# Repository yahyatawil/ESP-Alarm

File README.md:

# ESP-Alarm
This project was built for [Allaboutcircuit](https://www.allaboutcircuits.com/projects/esp-alarm-set-alarms-from-your-mobile-phone-esp8266-arduino-uno-wifi-iot/) published in 2017. 

## Hardware 
* Arduino UNO or any compatible board (optional).
* ATmega328P (optional).
* ESP8266 Wi-Fi module, ESP-01 model.
* 1.44-inch TFT display module.
* TP4056 breakout board (Li-ion battery charger).
* DS1307 (RTC chip)
* 74LVX4245 (5V-3V3 level converter)
* USB TTL converter cable (optional)

## Software / Arduino code
The code depends on the following libraries:

* TFT_ILI9163
* Adafruit_GFX
* DS1307RTC
* Wire (for I2C connection)
* EEPROM (to store alarms in the internal EEPROM)
* SoftwareSerial (optional debugging)

## Android App 

Many thanks to my friend Jihad Al-bathish (AKA Joud) for developing a native Android application for this project.

## Demo
https://www.youtube.com/watch?v=W3wOcIKqi2k

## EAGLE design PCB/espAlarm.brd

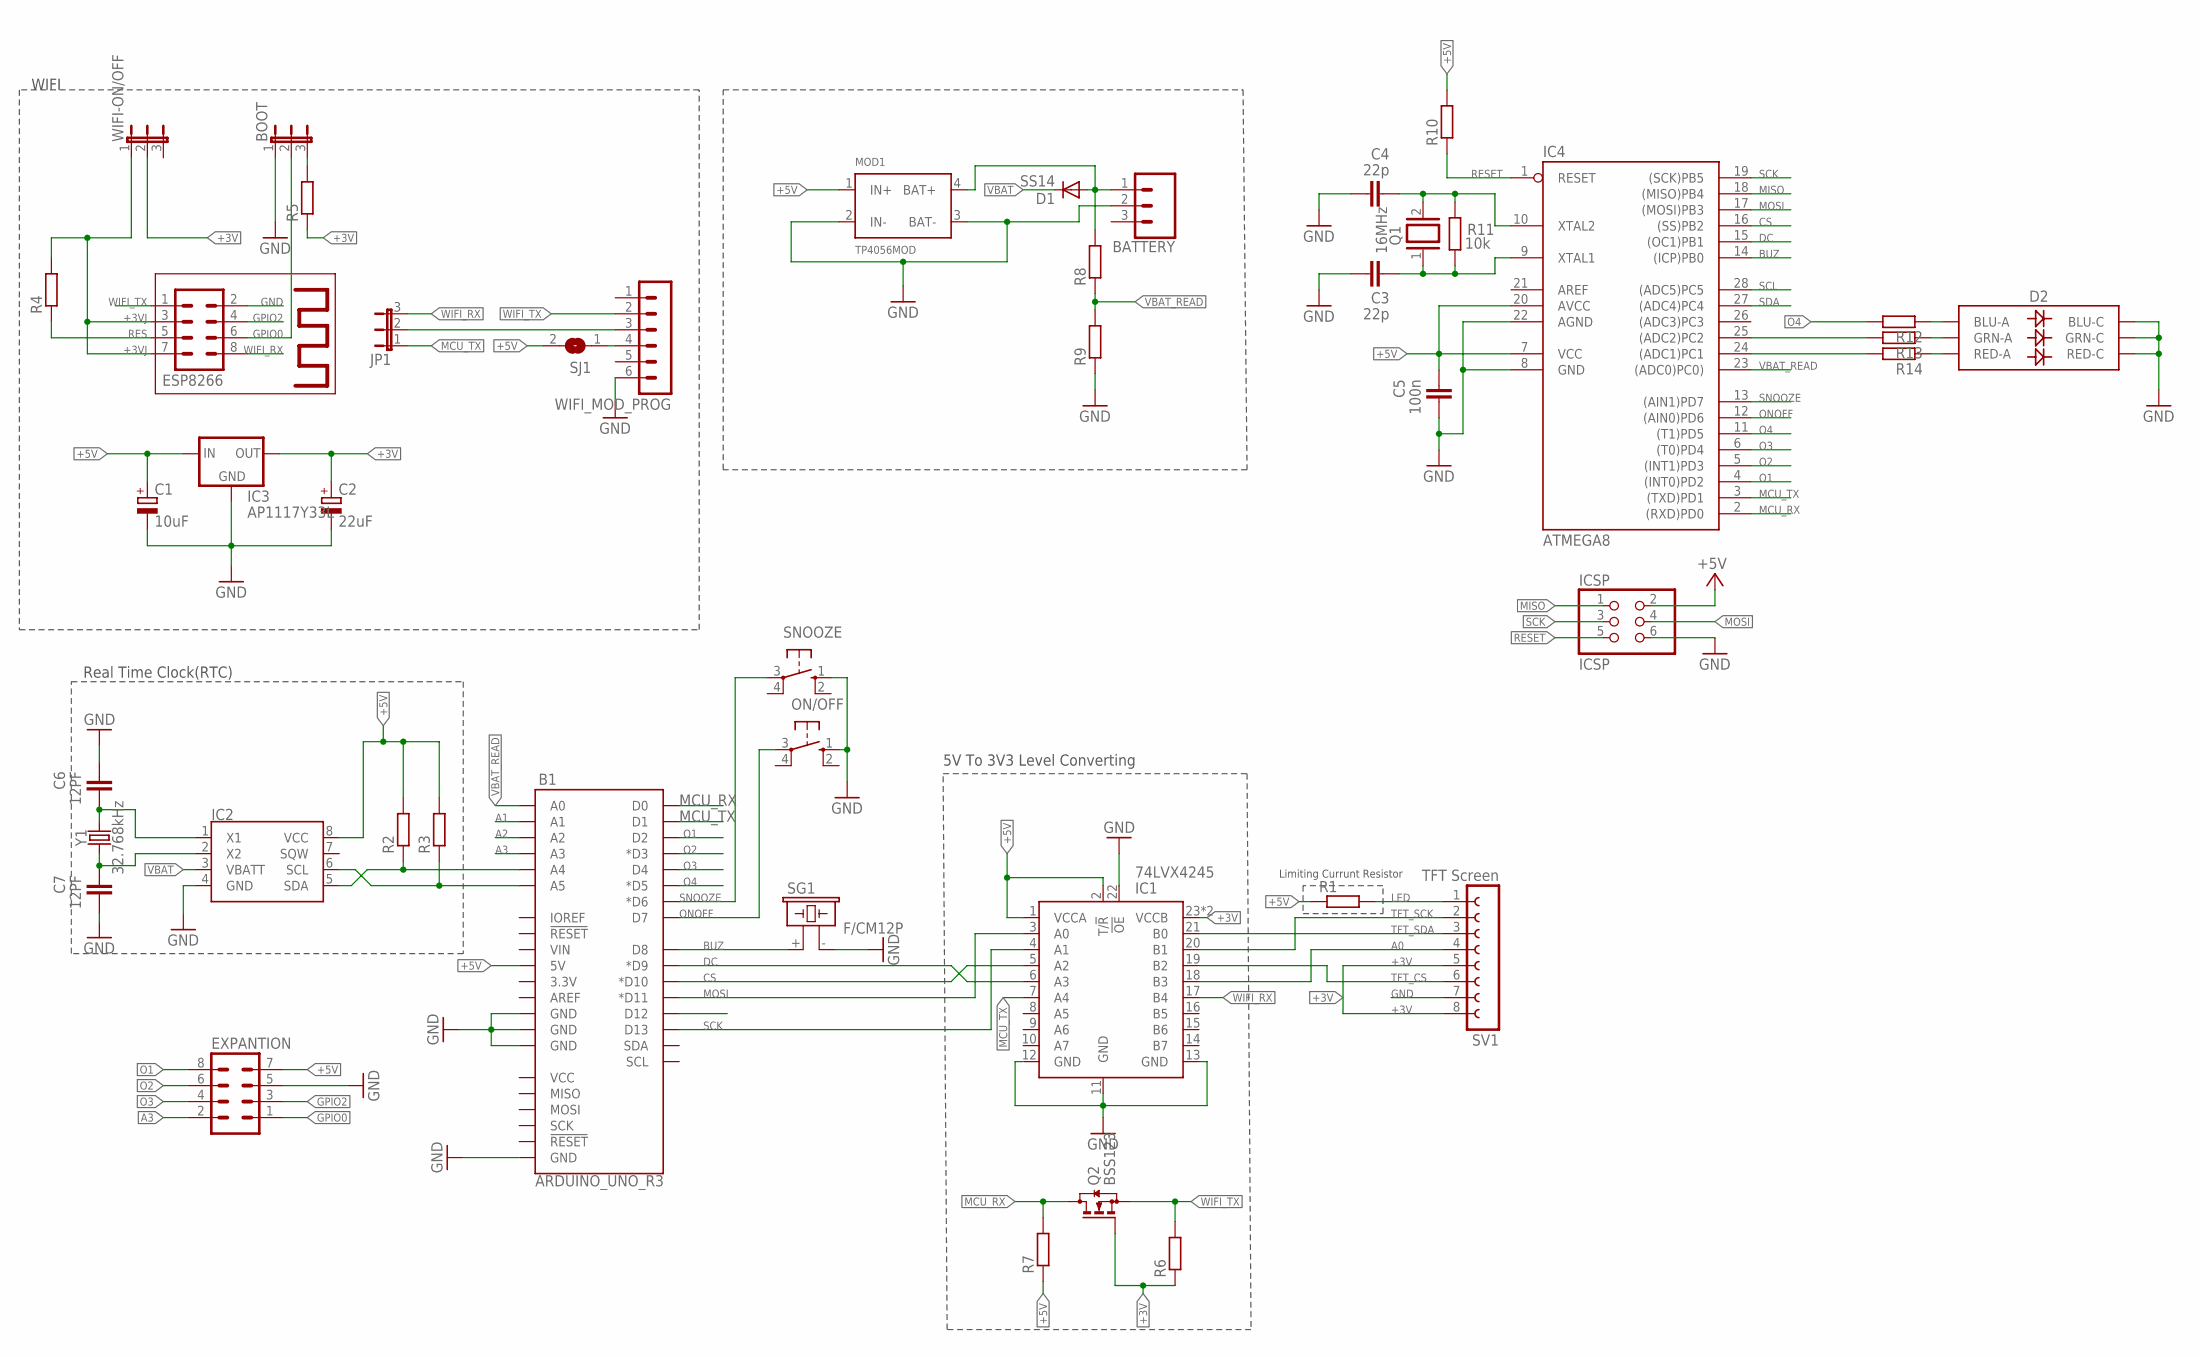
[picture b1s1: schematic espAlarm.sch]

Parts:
B1: ARDUINO_UNO_R3; ARDUINO_R3
BATTERY: CONN_03JST-PTH-VERT; JST-3-PTH-VERT
BOOT: JP2E; JP2
C1: 10uF; E2,5-7
C2: 22uF; E2,5-7
C3, C4: 22p; C0805
C5: 100n; C0805
C6, C7: 12PF; C0805
D1: SS14; DO214AC
D2: LED-RGBNO_IC; LED-TRICOLOR-5050
ESP8266: MA04-2
EXPANTION: MA04-2
IC1: 74LVX4245; TSSOP-24
IC2: DS1307; DIP-08
IC3: AP1117Y33L; SOT-89-3
IC4: ATMEGA8; DIL28-3
ICSP: ICSP; 2X03
JP1: JP2E; JP2
MOD1: TP4056MOD; TP4056BRD
ON/OFF: 10-XX; B3F-10XX
Q1: 16MHz; SMARTPRJ_QS
Q2: BSS123; SOT23
R1, R2, R3, R4, R5, R6, R7, R8, R9, R10, R12, R13, R14: R-EU_M1206; M1206
R11: 10k; M1206
SG1: F/CM12P
SJ1: SJ
SNOOZE: 10-XX; B3F-10XX
SV1: TFT Screen; FE08
WIFI-ON/OFF: JP2E; JP2
WIFI_MOD_PROG: MA06-1
Y1: 32.768kHz; CRYSTAL-PTH-2X6-CYL

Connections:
+3V: C2.+, IC1.23 (VCCB), IC1.24 (VCCB), IC3.3 (OUT), IC3.4 (OUT), Q2.1 (G), R5.1, R6.1, SV1.5, SV1.8, WIFI-ON/OFF.2
+3VJ: ESP8266.3, ESP8266.7, R4.2, WIFI-ON/OFF.1
+5V: B1.5V, C1.+, C5.2, EXPANTION.7, IC1.1 (VCCA), IC1.2 (T/!R), IC2.8 (VCC), IC3.1 (IN), IC4.7 (VCC), IC4.20 (AVCC), ICSP.2, MOD1.1 (IN+), R1.1, R2.2, R3.2, R7.1, R10.2, SJ1.2
A0: IC1.18 (B3), SV1.4
A1: B1.A1, IC4.24 ((ADC1)PC1), R14.2
A2: B1.A2, IC4.25 ((ADC2)PC2), R13.2
A3: B1.A3, EXPANTION.2
AREF: IC4.21 (AREF)
BUZ: B1.D8, IC4.14 ((ICP)PB0), SG1.+ (1)
CS: B1.D10 (*D10), IC1.5 (A2), IC4.16 ((SS)PB2)
DC: B1.D9 (*D9), IC1.6 (A3), IC4.15 ((OC1)PB1)
GND: B1.GND@1 (GND), B1.GND@2 (GND), B1.GND@3 (GND), B1.GND@4 (GND), BATTERY.2, BOOT.1, C1.-, C2.-, C3.1, C4.1, C5.1, C6.2, C7.1, D2.4 (BLU-C), D2.5 (RED-C), D2.6 (GRN-C), ESP8266.2, EXPANTION.5, IC1.11 (GND), IC1.12 (GND), IC1.13 (GND), IC1.22 (!OE), IC2.4 (GND), IC3.2 (GND), IC4.8 (GND), IC4.22 (AGND), ICSP.6, MOD1.2 (IN-), MOD1.3 (BAT-), ON/OFF.1 (S), R9.1, SG1.- (2), SNOOZE.1 (S), SV1.7, WIFI_MOD_PROG.6
GPIO0: BOOT.2, ESP8266.6, EXPANTION.1
GPIO2: ESP8266.4, EXPANTION.3
LED: R1.2, SV1.1
MCU_RX: B1.D0, IC4.2 ((RXD)PD0), Q2.3 (D), R7.2
MCU_TX: B1.D1, IC1.7 (A4), IC4.3 ((TXD)PD1), JP1.1
MISO: IC4.18 ((MISO)PB4), ICSP.1
MOSI: B1.D11 (*D11), IC1.3 (A0), IC4.17 ((MOSI)PB3), ICSP.4
unnamed: JP1.2, WIFI_MOD_PROG.3
unnamed: BOOT.3, R5.2
unnamed: C6.1, IC2.1 (X1), Y1.2
unnamed: C7.2, IC2.2 (X2), Y1.1
unnamed: SJ1.1, WIFI_MOD_PROG.4
unnamed: BATTERY.1, D1.A, MOD1.4 (BAT+), R8.2
unnamed: C3.2, IC4.9 (XTAL1), Q1.1, R11.1
unnamed: C4.2, IC4.10 (XTAL2), Q1.2, R11.2
unnamed: D2.3 (BLU-A), R12.1
unnamed: D2.1 (GRN-A), R13.1
unnamed: D2.2 (RED-A), R14.1
O1: B1.D2, EXPANTION.8, IC4.4 ((INT0)PD2)
O2: B1.D3 (*D3), EXPANTION.6, IC4.5 ((INT1)PD3)
O3: B1.D4, EXPANTION.4, IC4.6 ((T0)PD4)
O4: B1.D5 (*D5), IC4.11 ((T1)PD5), R12.2
ONOFF: B1.D7, IC4.12 ((AIN0)PD6), ON/OFF.3
RES: ESP8266.5, R4.1
RESET: IC4.1 (RESET), ICSP.5, R10.1
SCK: B1.D13, IC1.4 (A1), IC4.19 ((SCK)PB5), ICSP.3
SCL: B1.A5, IC2.6 (SCL), IC4.28 ((ADC5)PC5), R3.1
SDA: B1.A4, IC2.5 (SDA), IC4.27 ((ADC4)PC4), R2.1
SNOOZE: B1.D6 (*D6), IC4.13 ((AIN1)PD7), SNOOZE.3
TFT_CS: IC1.19 (B2), SV1.6
TFT_SCK: IC1.20 (B1), SV1.2
TFT_SDA: IC1.21 (B0), SV1.3
VBAT: D1.C, IC2.3 (VBATT)
VBAT_READ: B1.A0, IC4.23 ((ADC0)PC0)), R8.1, R9.2
WIFI_RX: ESP8266.8, IC1.17 (B4), JP1.3
WIFI_TX: ESP8266.1, Q2.2 (S), R6.2, WIFI_MOD_PROG.2

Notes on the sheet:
5V To 3V3 Level Converting
Limiting Currunt Resistor
Real Time Clock(RTC)
WIFI

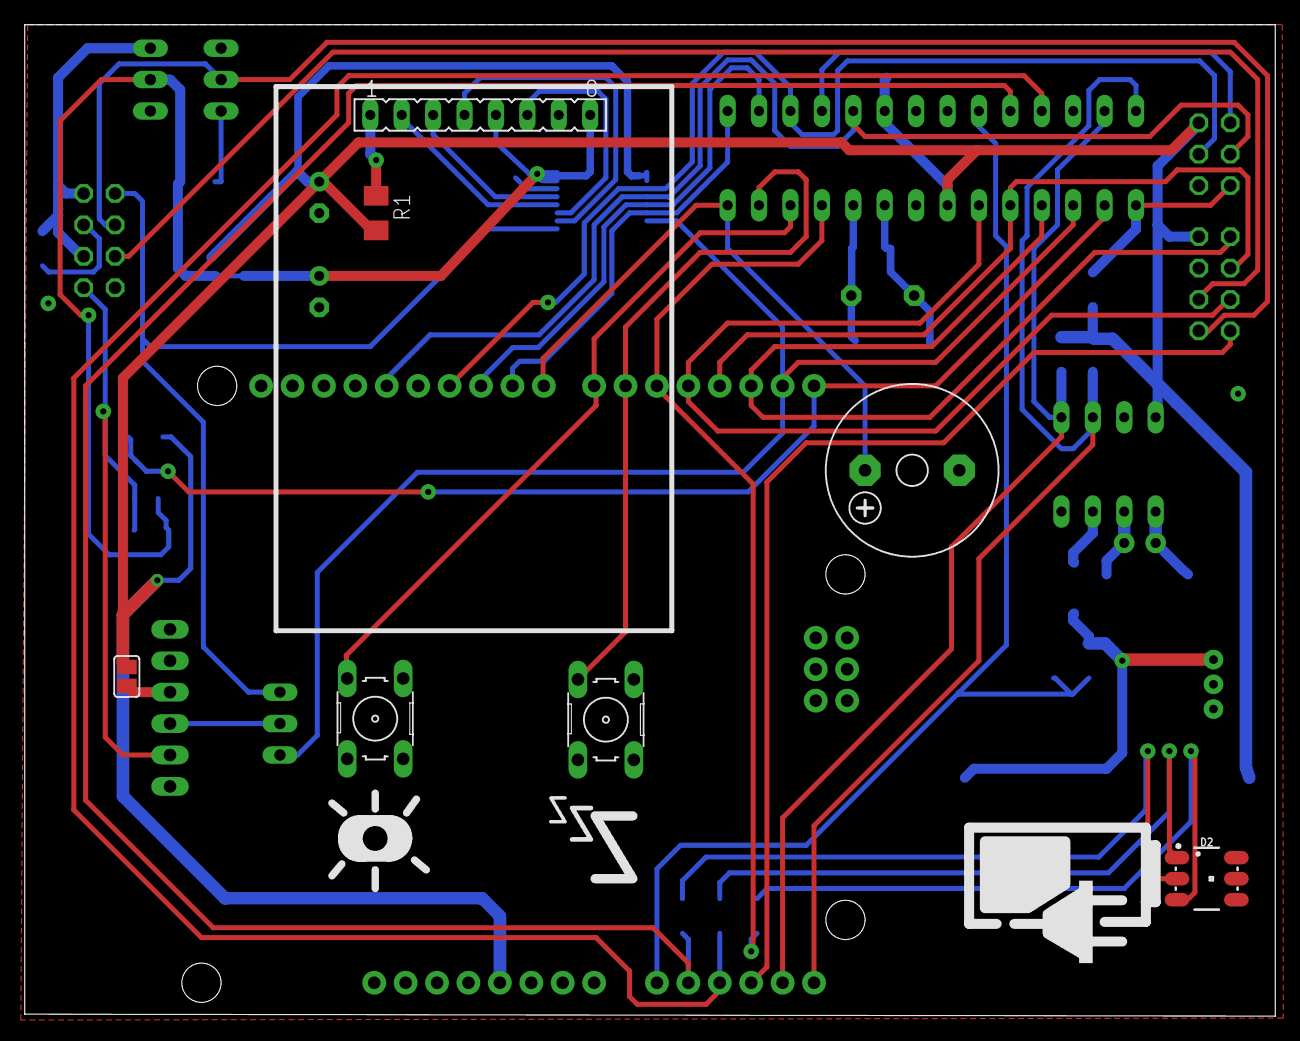
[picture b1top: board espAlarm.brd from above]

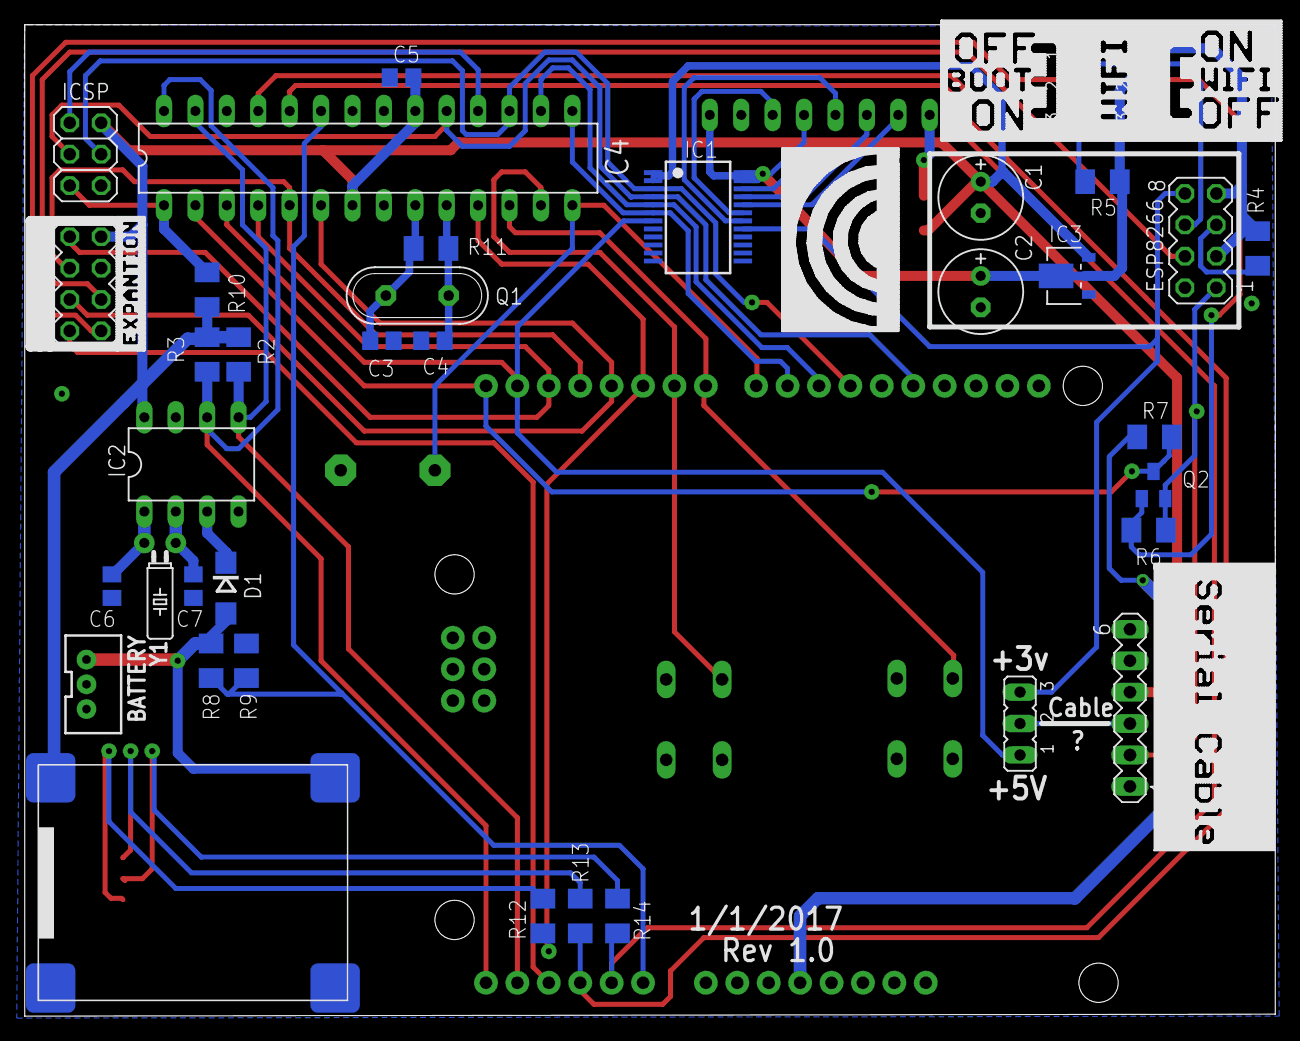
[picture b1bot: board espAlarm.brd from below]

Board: 2 copper layers, 101.1 x 80.2 mm, 45 parts (37 on the bottom side), 47 nets.

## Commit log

2023-10-17 Source files

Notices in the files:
parts and their libraries:
SparkFun-Boards: Licensing: Creative Commons ShareAlike 4.0 International - https://creativecommons.org/licenses/by-sa/4.0
